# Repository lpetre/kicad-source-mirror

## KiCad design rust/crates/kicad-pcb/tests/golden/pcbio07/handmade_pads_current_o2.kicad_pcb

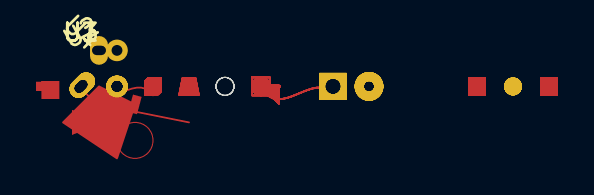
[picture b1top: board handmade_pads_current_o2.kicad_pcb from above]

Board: 4 copper layers, 4 parts (1 on the bottom side), 2 nets, no tracks yet.

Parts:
U1: V1; FP1
U2: V2; FP2
U3: V3; FP3
U4: V4; FP4

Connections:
GND: U1.1 (GND), U1.9, U3.1 (GND), U3.9, U4.1 (GND), U4.9
SIG: U1.2, U1.3, U3.2, U3.3, U4.2, U4.3
